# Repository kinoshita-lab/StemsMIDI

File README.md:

# STEMS MIDI: MIDI Controller for Traktor Stems (Dev board)

[日本語はこちら(Document in Japanese)](./README.ja.md)

## ChangeLog
### Software
releases (https://github.com/kinoshita-lab/StemsMIDI/releases)

### Hardware Rev. 1.1
- [Hardware] Remove center-click feature for Vol and Effect knobs
- [Hardware] Add testing terminals on PCB

## Kit Contents

- Pre-assembled PCB
- MCU Module Seeeduino XIAO RP2040(with flashed "sample" program)
- Pin Socket 1x7 (2 pcs.)
- Pin Header 1x7 (2 pcs.)
- Knob Caps (24 pcs.)
- Tactile switch Caps (24 pcs.)
- M3 Nuts (6 pcs.)
- M3 10mm Hex Spacers (6 pcs.)
- M3 7mm Hex Spacers (6 pcs.)
- M3 Screws (6 pcs.)
- Rubber feet pads(4 pcs.)
- Bottom Acrylic Panel (1 pcs.)
- Top Acrylic Panel (1 pcs.)

## Requied Equipments

- Solder Iron, Solder
- No.2 + Driver
- Plier and/or Wrench (for tightening nuts)

## How to assemble

### Assemble the MCU Module

Recommend following procedure to align pins.
tips: You can solder MCU Module directly on the PCBA board.

Solder Pin Sockets, Pin Headers, and MCU. 1st, combine Pin Sockets and Headers as show below:

Put above result into MCU's both side holes as shown below:

Put them on the holes of PCBA below:

Solder the Pin Header's MCU side:

Looks like below:

Put it again on the PCBA's holes:

Flip the PCBA board while holding the MCU module, with placing knob cap between MCU and the desk so that it can be held in place by its own weight.

Looks like below:

Solder all the Pin socket's pin:

### Assembling case

Peel off the protective sheet from the bottom acrylic panel, and attach nuts, M3  7mm Hex spacers hex screws (the shorter ones) at six locations.
(There are no two sides to the acrylic.):

Put PCBA bord on it, tighten with the M3 10mm hex screws (the longer ones).
Tighten each screw little by little at to align the overall position:

Peel of the protective sheet from top acrylic panel and put it on the PCBA.
Tighten them with M3 screws.
Again, tighten each screw little by little at to align the overall position:

Put rubber feets on the bottom:

Place knob caps:

Place tactile switch caps:

## Usage

- Connect the product to PC/MAC.
- Import .tsi file below on Traktor.

<https://github.com/kinoshita-lab/StemsMIDI/tree/main/Traktor%20Setting>

## How to update Software

What you will need:

- Latest software to be flashed to the MCU(firmware.uf2) download from <https://github.com/kinoshita-lab/StemsMIDI/releases>
- PC or mac

Connect the USB cable with pressing the **B** button on the right bottom of the MCU.

After releasing the button, disk drive will appear on you PC/mac. The drive name is `RP-RP2`.

Copy the firmware.uf2 file to the drive.

Done updating, drive will automatically closed.

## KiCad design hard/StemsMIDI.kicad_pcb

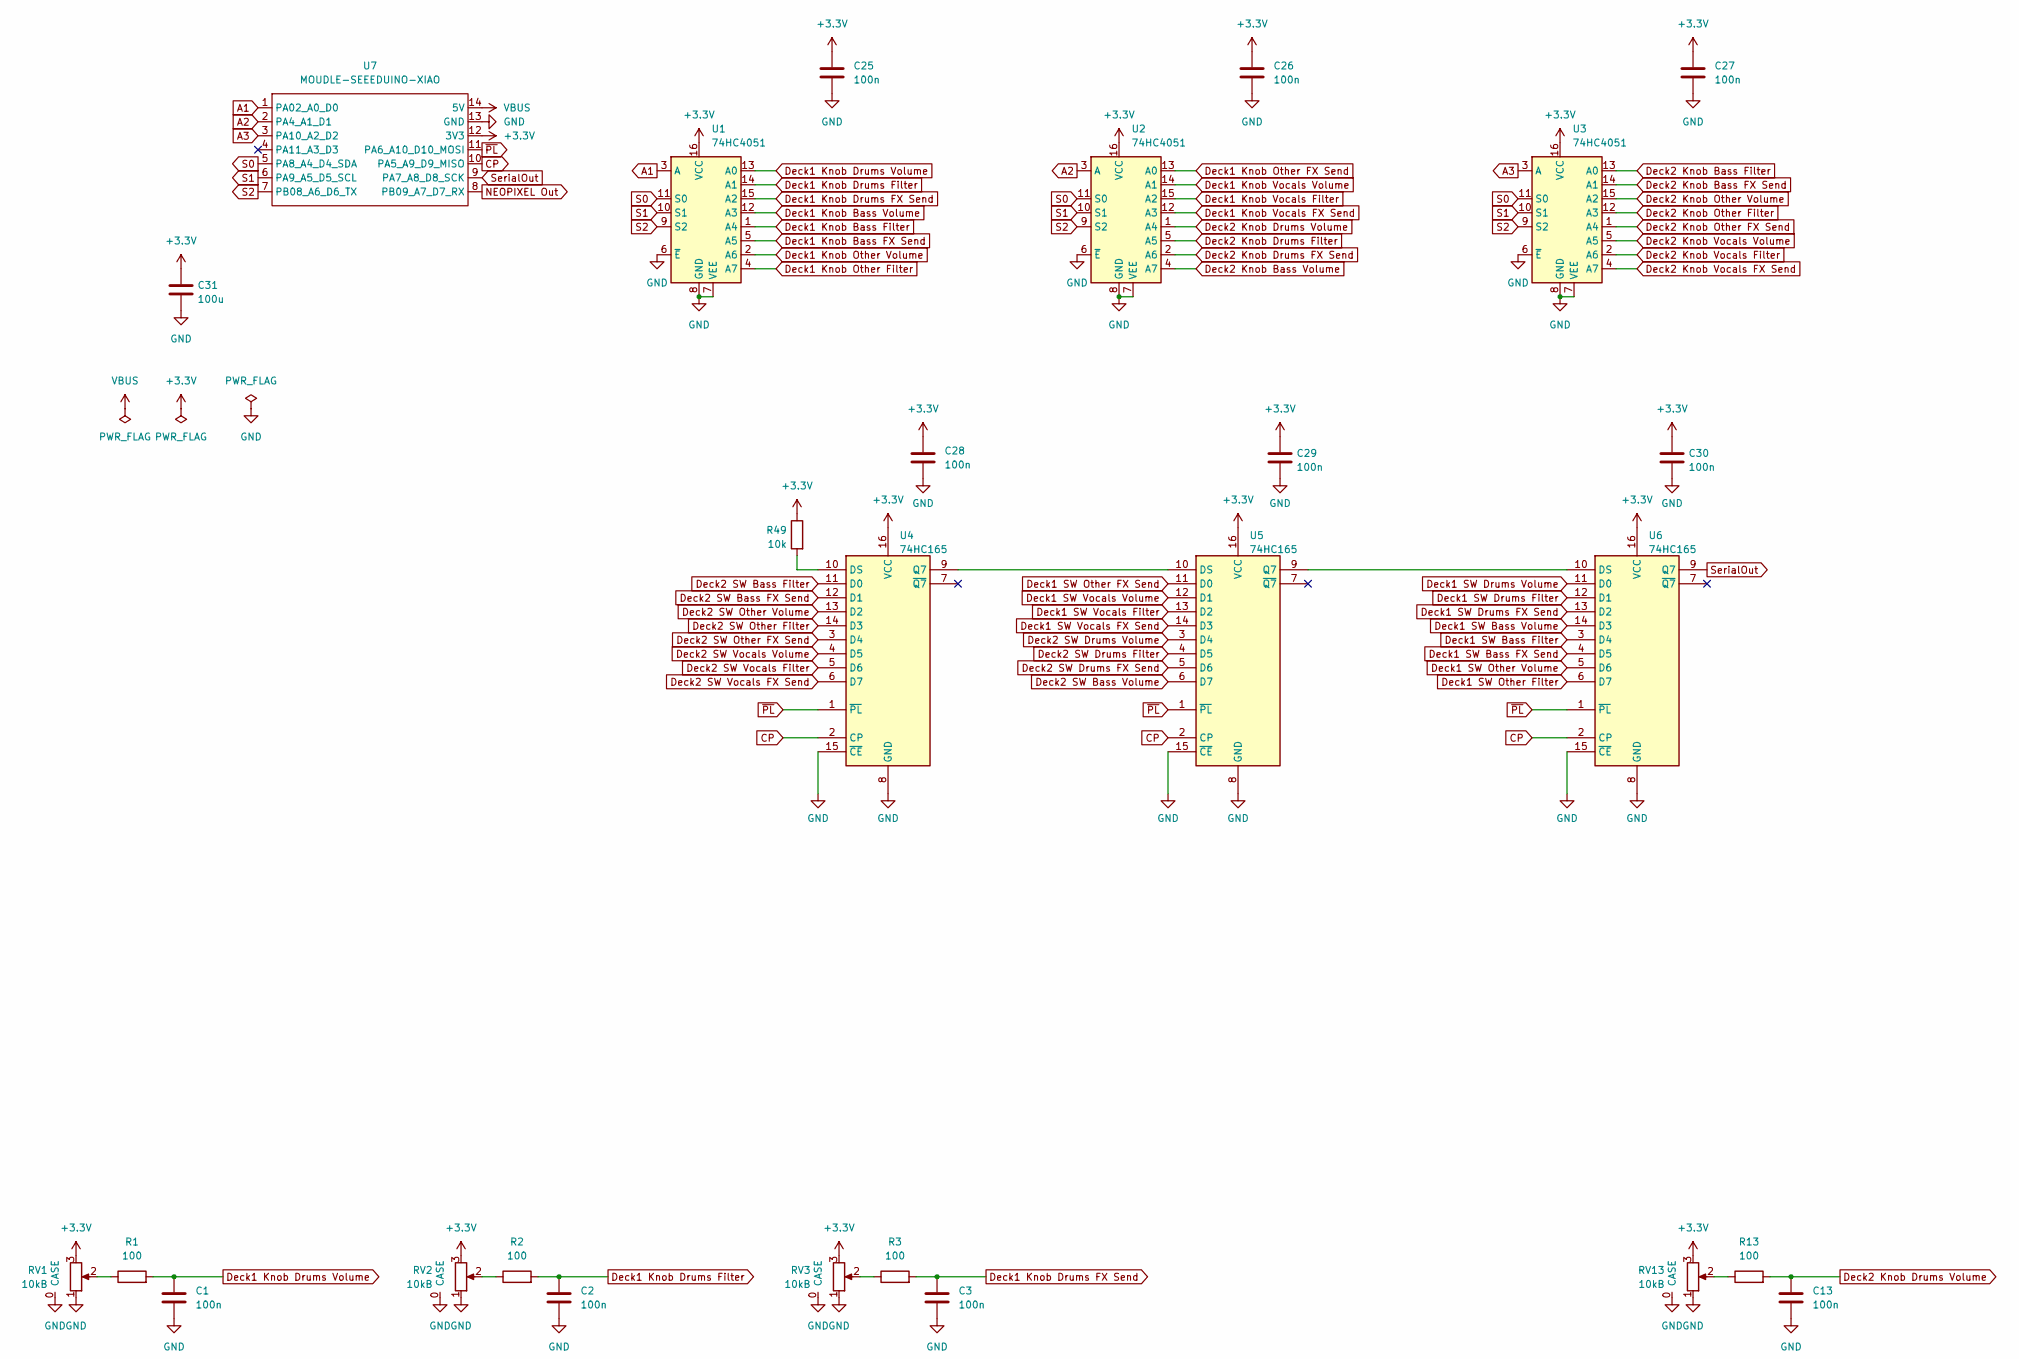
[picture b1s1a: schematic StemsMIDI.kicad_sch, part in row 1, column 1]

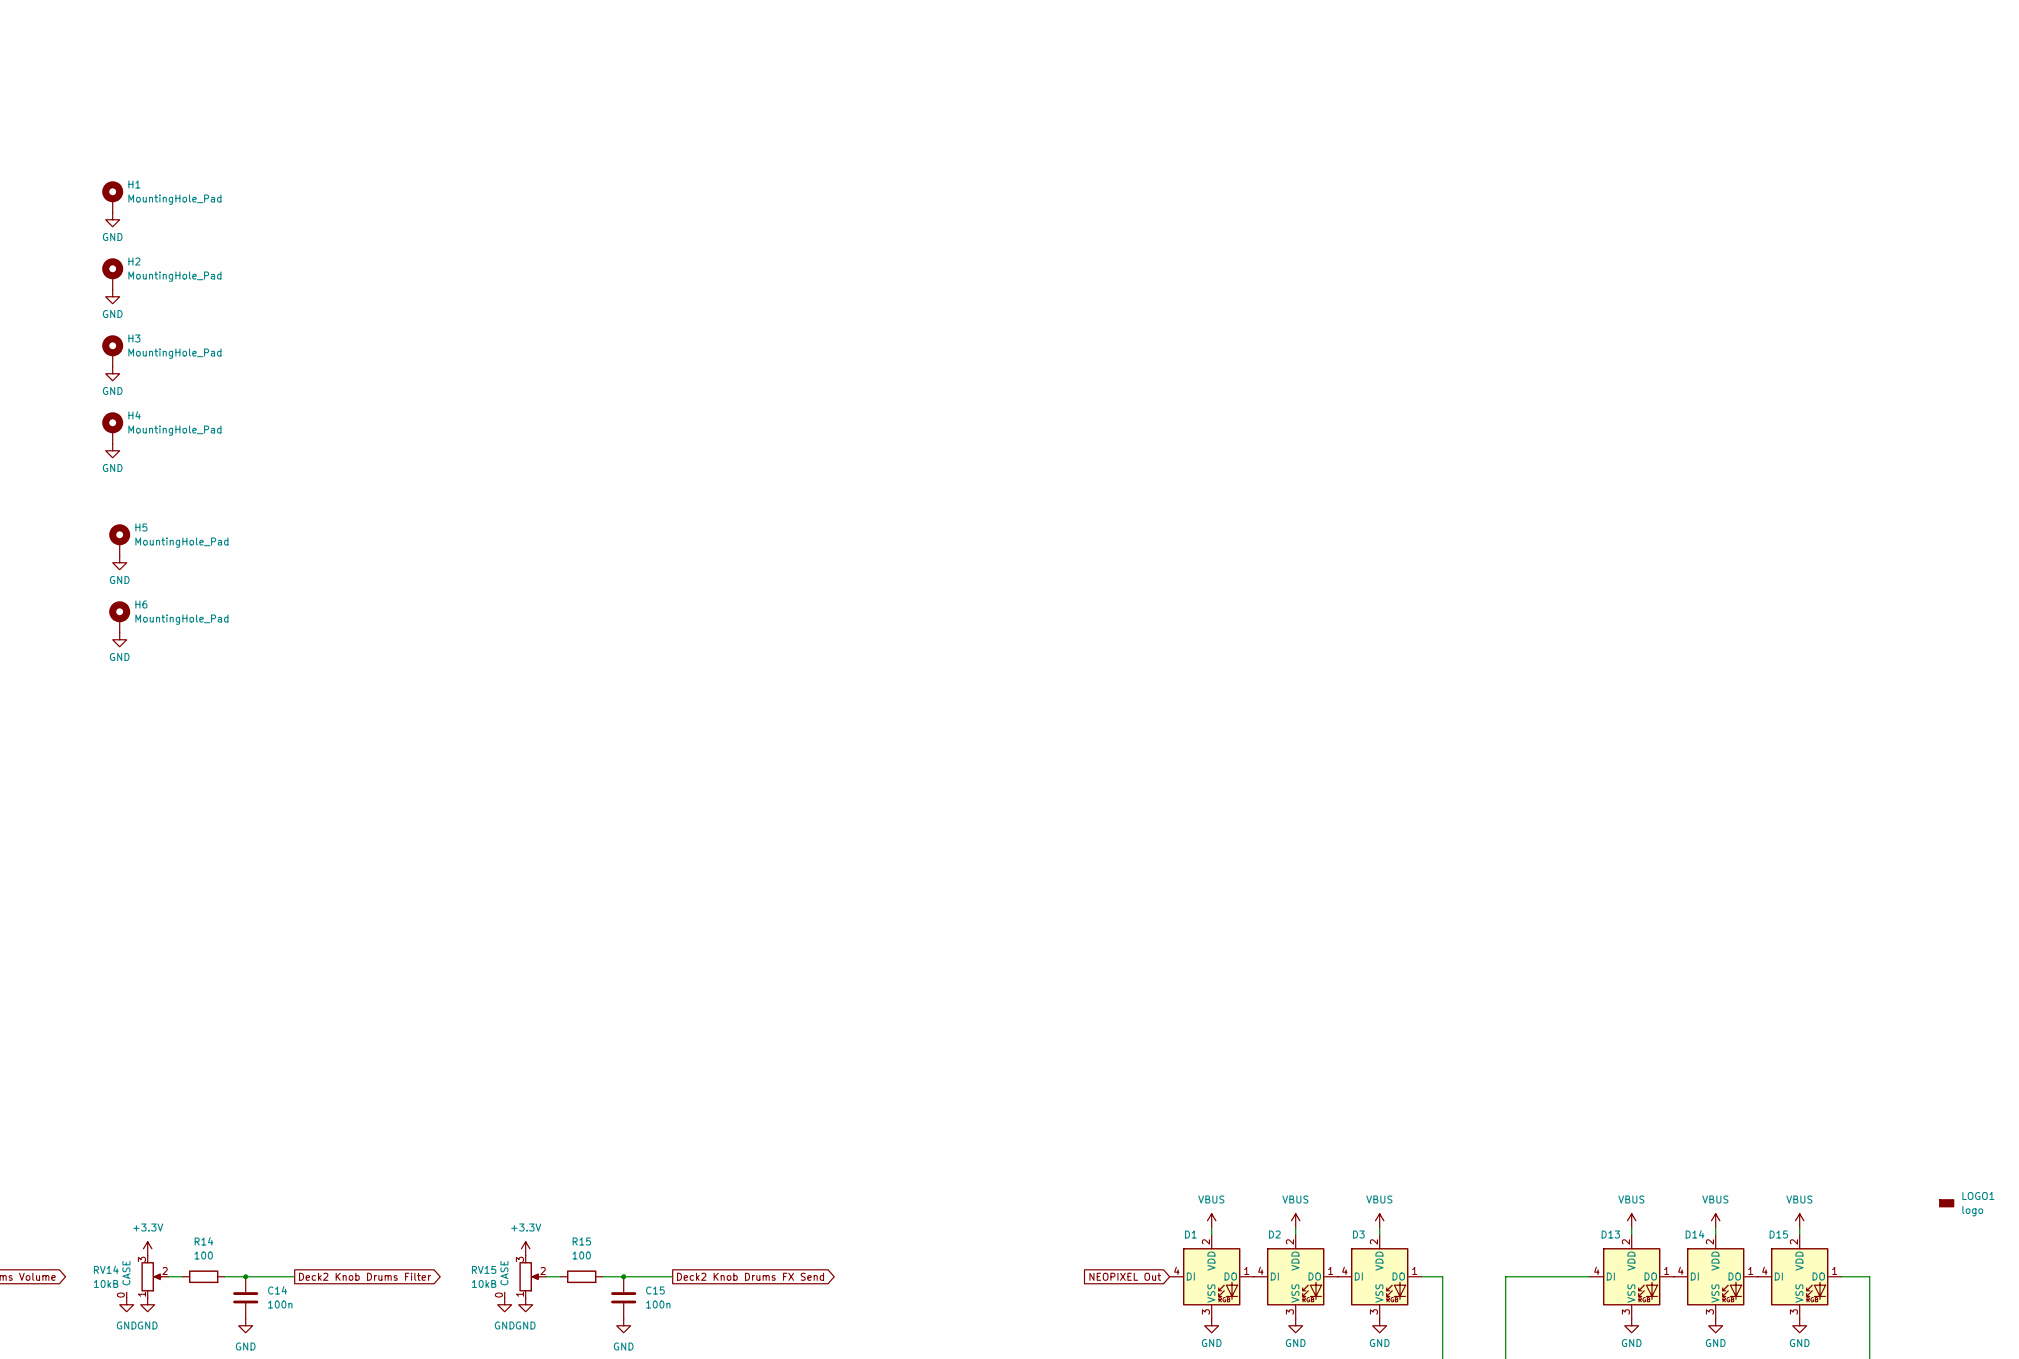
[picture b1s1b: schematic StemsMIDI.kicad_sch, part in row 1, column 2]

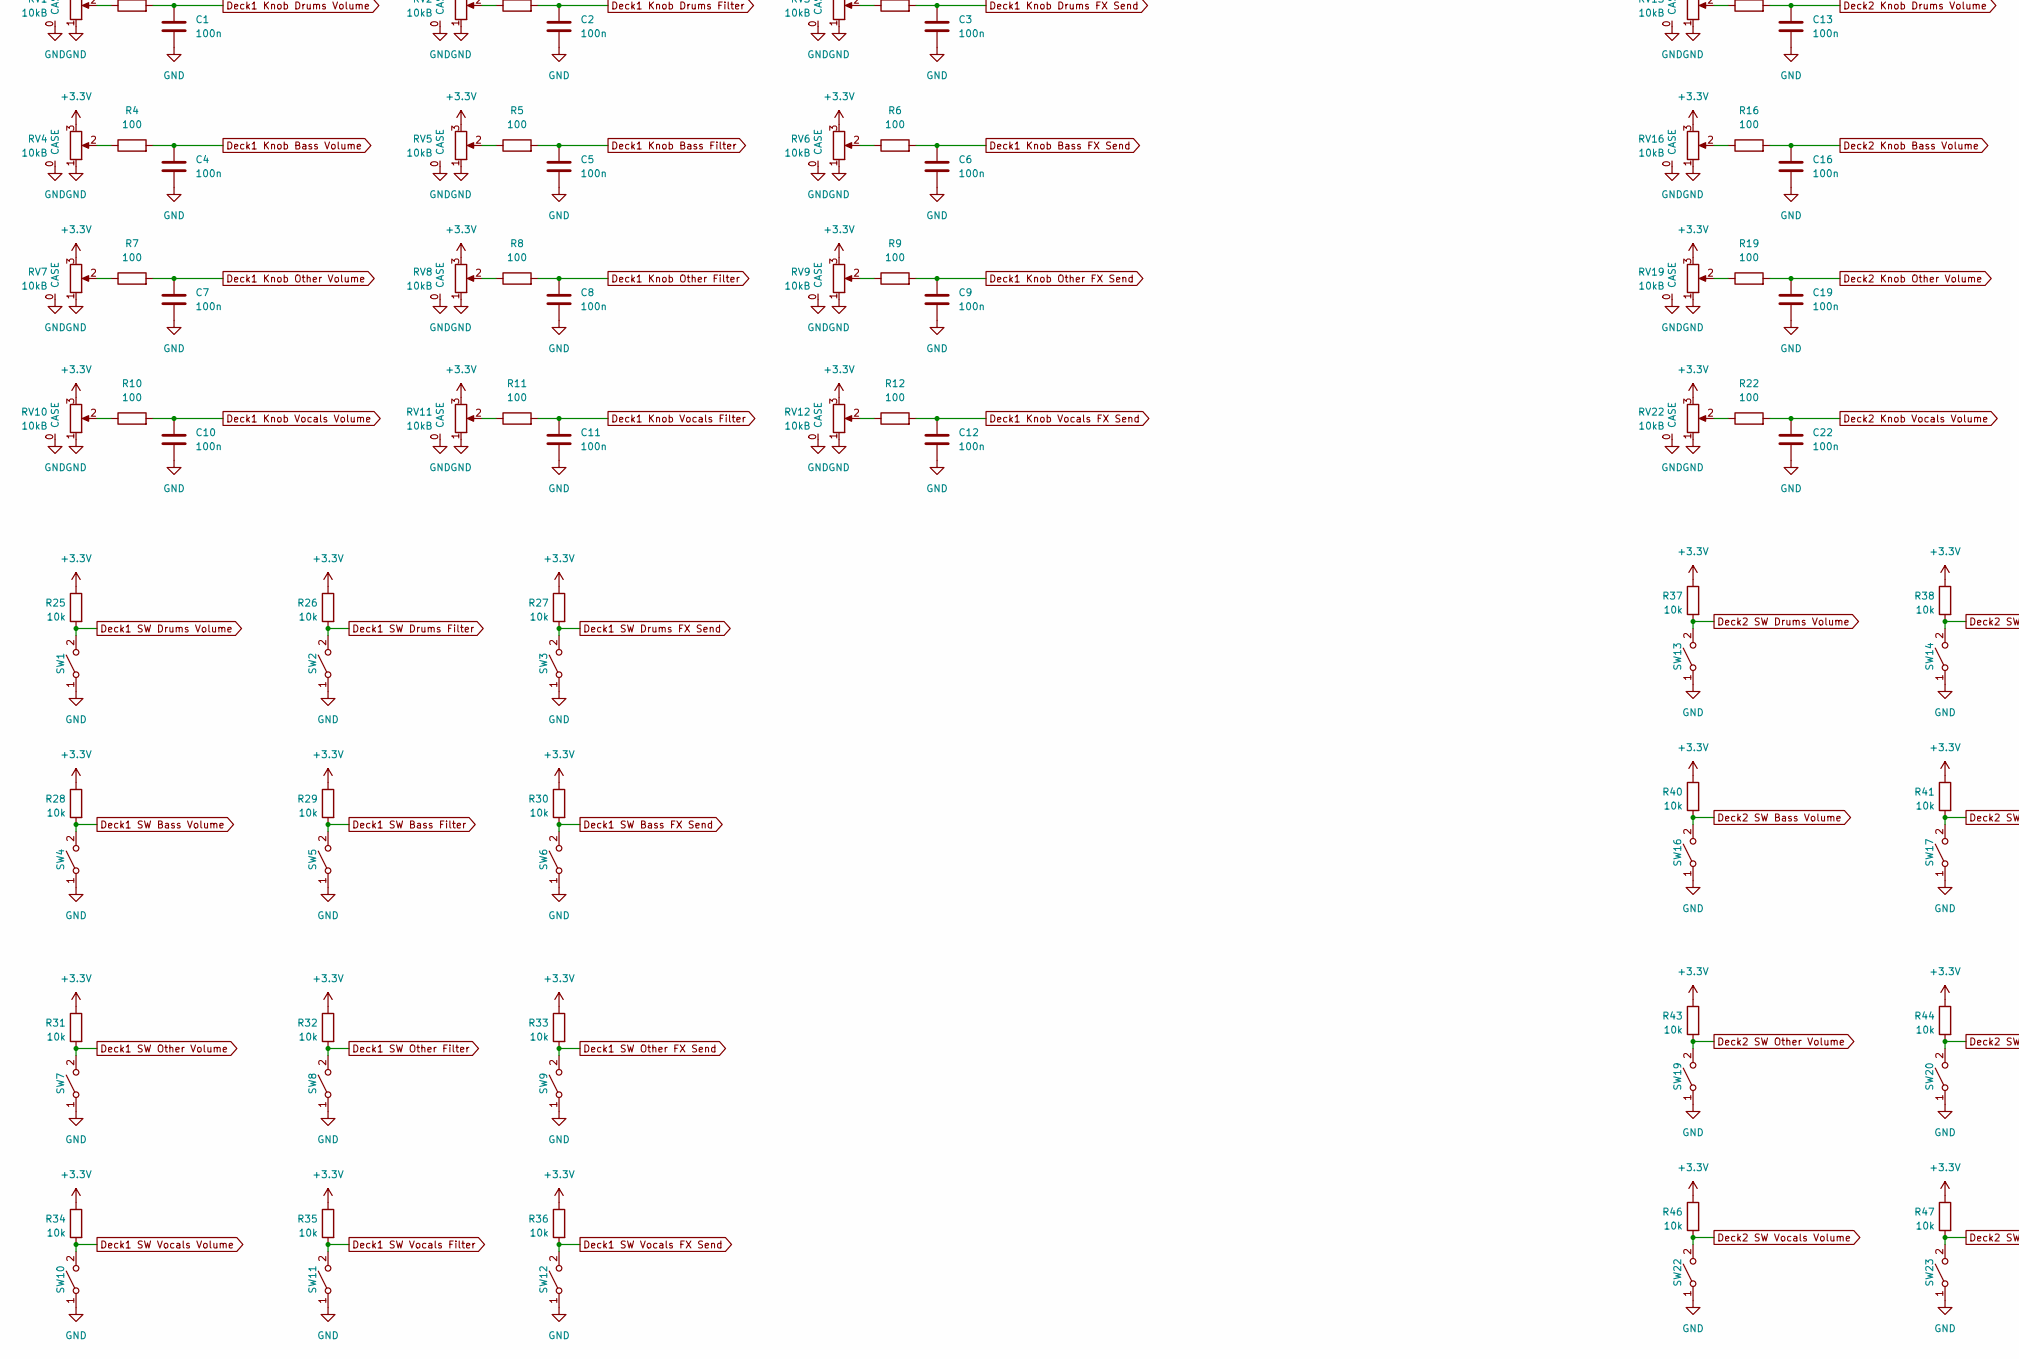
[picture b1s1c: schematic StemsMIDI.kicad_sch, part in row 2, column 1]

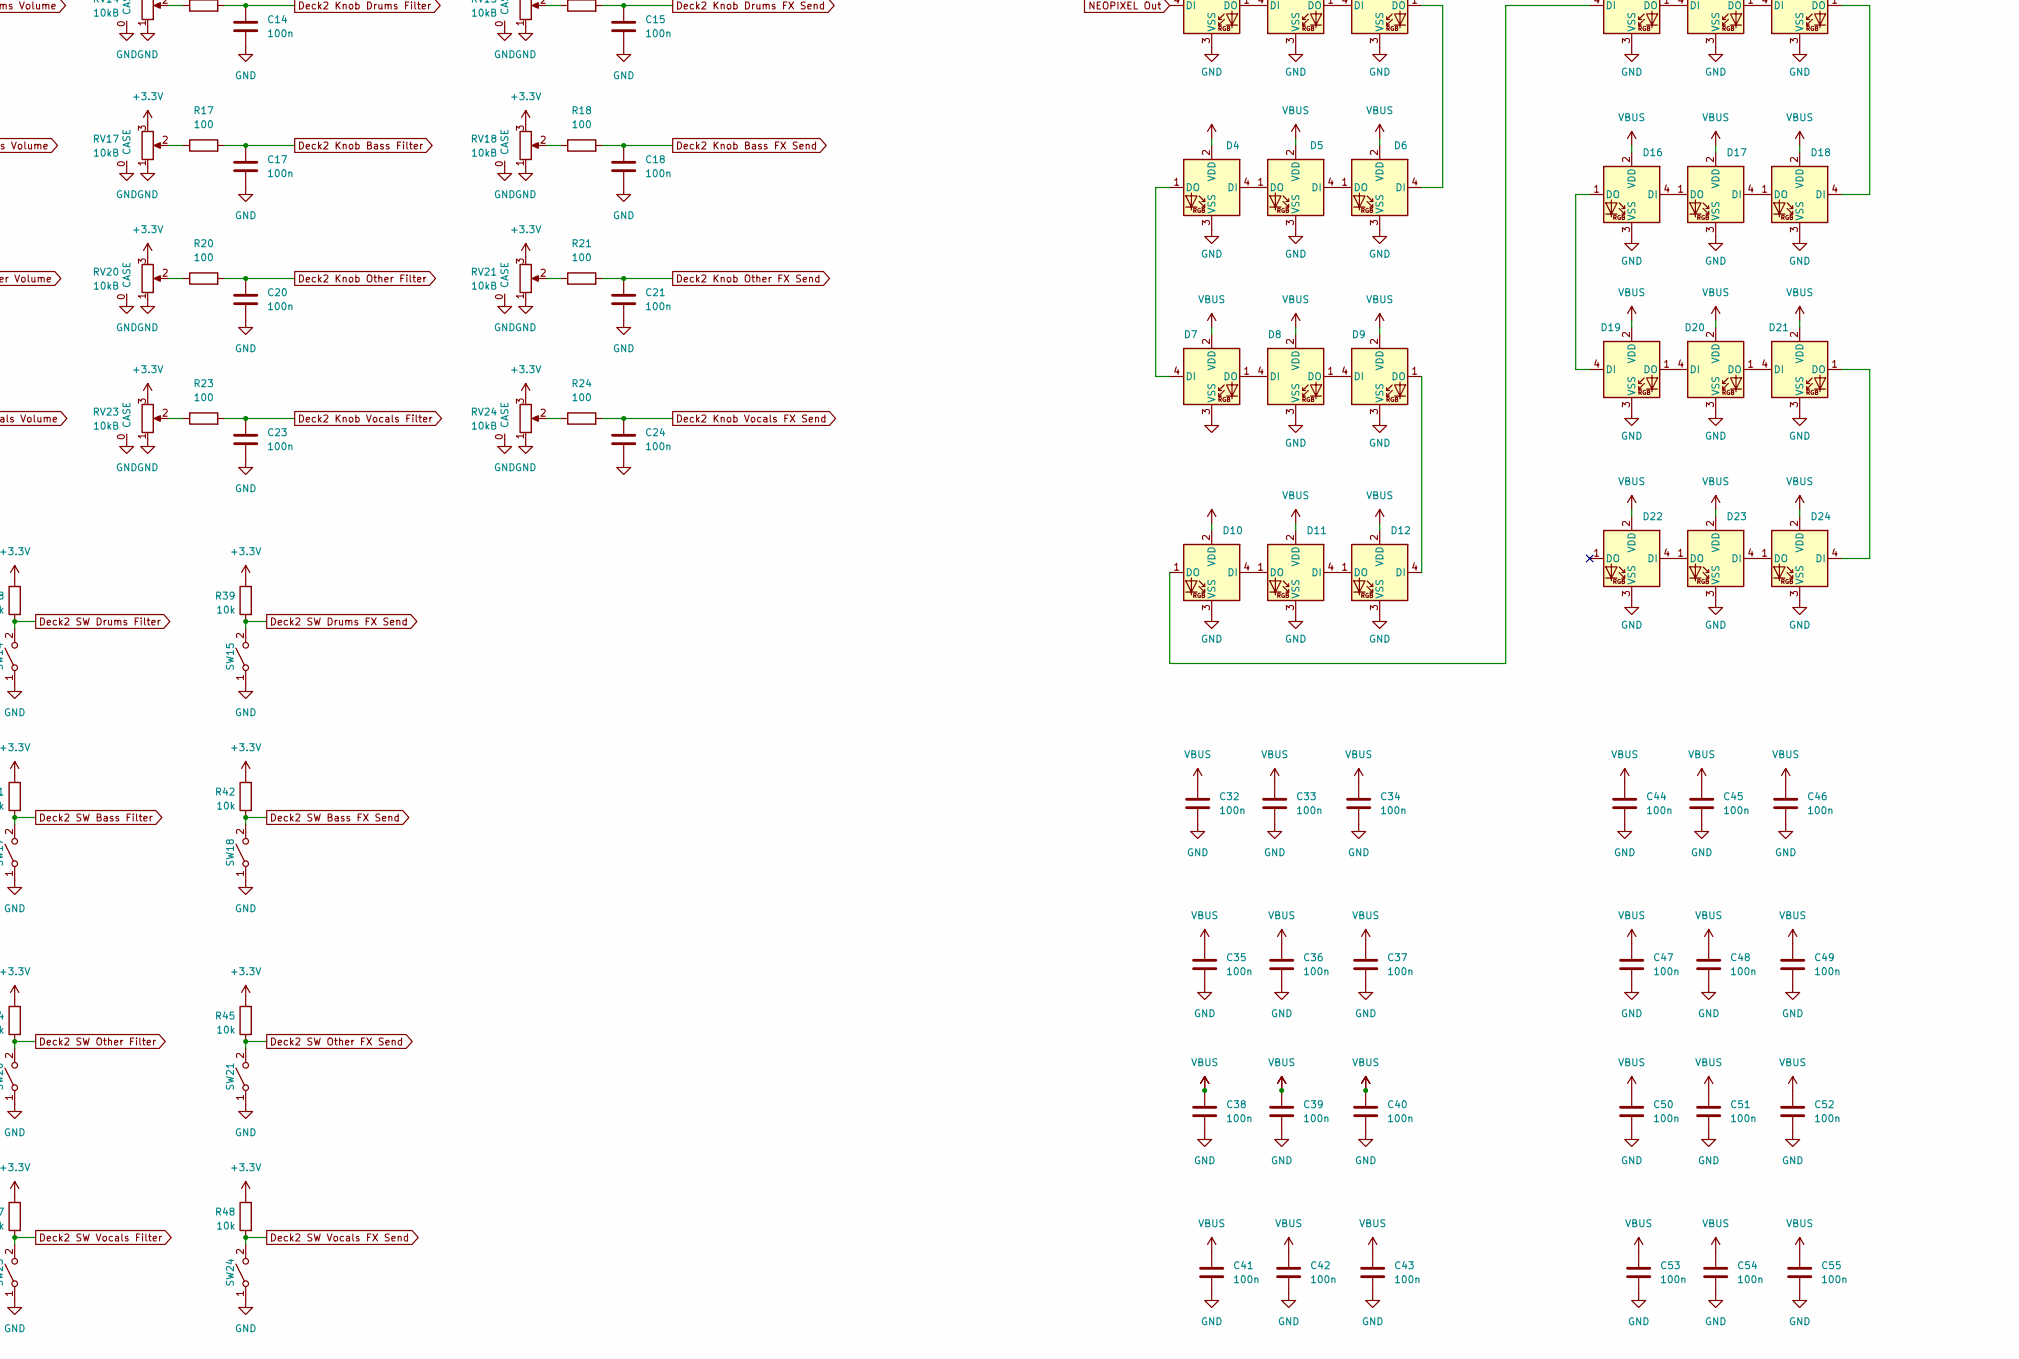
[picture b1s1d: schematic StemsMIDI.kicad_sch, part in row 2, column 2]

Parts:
C1, C2, C3, C4, C5, C6, C7, C8, C9, C10, C11, C12, C13, C14, C15, C16, C17, C18, C19, C20, C21, C22, C23, C24, C25, C26, C27, C28, C29, C30, C32, C33, C34, C35, C36, C37, C38, C39, C40, C41, C42, C43, C44, C45, C46, C47, C48, C49, C50, C51, C52, C53, C54, C55: 100n; C_0402_1005Metric_Pad0.74x0.62mm_HandSolder; LCSC C1525
C31: 100u; C_1206_3216Metric_Pad1.33x1.80mm_HandSolder; LCSC C312983
D1, D2, D3, D4, D5, D6, D7, D8, D9, D10, D11, D12, D13, D14, D15, D16, D17, D18, D19, D20, D21, D22, D23, D24: LED_NeoPixel_XL-1615RGBC-WS2812B; LCSC C5349954
H1, H2, H3, H4, H5, H6: MountingHole_Pad; MountingHole_3.2mm_M3_Pad
LOGO1: logo; kinoshita-logo_simplified_300dpi
R1, R2, R3, R4, R5, R6, R7, R8, R9, R10, R11, R12, R13, R14, R15, R16, R17, R18, R19, R20, R21, R22, R23, R24: 100; R_0402_1005Metric_Pad0.72x0.64mm_HandSolder; LCSC C106232
R25, R26, R27, R28, R29, R30, R31, R32, R33, R34, R35, R36, R37, R38, R39, R40, R41, R42, R43, R44, R45, R46, R47, R48, R49: 10k; R_0402_1005Metric_Pad0.72x0.64mm_HandSolder; LCSC C25744
RV1, RV2, RV3, RV4, RV5, RV6, RV7, RV8, RV9, RV10, RV11, RV12, RV13, RV14, RV15, RV16, RV17, RV18, RV19, RV20, RV21, RV22, RV23, RV24: 10kB; Potentiometer_Alps_RK09K_Horizontal_CORRECTED; LCSC C470315
SW1, SW2, SW3, SW4, SW5, SW6, SW7, SW8, SW9, SW10, SW11, SW12, SW13, SW14, SW15, SW16, SW17, SW18, SW19, SW20, SW21, SW22, SW23, SW24: SW_SPST; SW_Tactile_6mm_x_6mm_Futsuuno_SMD; LCSC C2885193
U1, U2, U3: 74HC4051; TSSOP-16_4.4x5mm_P0.65mm; LCSC C5645
U4, U5, U6: 74HC165; TSSOP-16_4.4x5mm_P0.65mm; LCSC C80696
U7: MOUDLE-SEEEDUINO-XIAO; Seeduino_Xiao_RP2040_MOUDLE14P-2.54-21X17.8MM

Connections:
+3.3V: C25.1, C26.1, C27.1, C28.1, C29.1, C30.1, C31.1, R25.1, R26.1, R27.1, R28.1, R29.1, R30.1, R31.1, R32.1, R33.1, R34.1, R35.1, R36.1, R37.1, R38.1, R39.1, R40.1, R41.1, R42.1, R43.1, R44.1, R45.1, R46.1, R47.1, R48.1, R49.1, RV1.3, RV2.3, RV3.3, RV4.3, RV5.3, RV6.3, RV7.3, RV8.3, RV9.3, RV10.3, RV11.3, RV12.3, RV13.3, RV14.3, RV15.3, RV16.3, RV17.3, RV18.3, RV19.3, RV20.3, RV21.3, RV22.3, RV23.3, RV24.3, U1.16 (VCC), U2.16 (VCC), U3.16 (VCC), U4.16 (VCC), U5.16 (VCC), U6.16 (VCC), U7.12 (3V3)
A1: U1.3 (A), U7.1 (PA02_A0_D0)
A2: U2.3 (A), U7.2 (PA4_A1_D1)
A3: U3.3 (A), U7.3 (PA10_A2_D2)
CP: U4.2 (CP), U5.2 (CP), U6.2 (CP), U7.10 (PA5_A9_D9_MISO)
Deck1 Knob Bass FX Send: C6.1, R6.2, U1.5 (A5)
Deck1 Knob Bass Filter: C5.1, R5.2, U1.1 (A4)
Deck1 Knob Bass Volume: C4.1, R4.2, U1.12 (A3)
Deck1 Knob Drums FX Send: C3.1, R3.2, U1.15 (A2)
Deck1 Knob Drums Filter: C2.1, R2.2, U1.14 (A1)
Deck1 Knob Drums Volume: C1.1, R1.2, U1.13 (A0)
Deck1 Knob Other FX Send: C9.1, R9.2, U2.13 (A0)
Deck1 Knob Other Filter: C8.1, R8.2, U1.4 (A7)
Deck1 Knob Other Volume: C7.1, R7.2, U1.2 (A6)
Deck1 Knob Vocals FX Send: C12.1, R12.2, U2.12 (A3)
Deck1 Knob Vocals Filter: C11.1, R11.2, U2.15 (A2)
Deck1 Knob Vocals Volume: C10.1, R10.2, U2.14 (A1)
Deck1 SW Bass FX Send: R30.2, SW6.2 (B), U6.4 (D5)
Deck1 SW Bass Filter: R29.2, SW5.2 (B), U6.3 (D4)
Deck1 SW Bass Volume: R28.2, SW4.2 (B), U6.14 (D3)
Deck1 SW Drums FX Send: R27.2, SW3.2 (B), U6.13 (D2)
Deck1 SW Drums Filter: R26.2, SW2.2 (B), U6.12 (D1)
Deck1 SW Drums Volume: R25.2, SW1.2 (B), U6.11 (D0)
Deck1 SW Other FX Send: R33.2, SW9.2 (B), U5.11 (D0)
Deck1 SW Other Filter: R32.2, SW8.2 (B), U6.6 (D7)
Deck1 SW Other Volume: R31.2, SW7.2 (B), U6.5 (D6)
Deck1 SW Vocals FX Send: R36.2, SW12.2 (B), U5.14 (D3)
Deck1 SW Vocals Filter: R35.2, SW11.2 (B), U5.13 (D2)
Deck1 SW Vocals Volume: R34.2, SW10.2 (B), U5.12 (D1)
Deck2 Knob Bass FX Send: C18.1, R18.2, U3.14 (A1)
Deck2 Knob Bass Filter: C17.1, R17.2, U3.13 (A0)
Deck2 Knob Bass Volume: C16.1, R16.2, U2.4 (A7)
Deck2 Knob Drums FX Send: C15.1, R15.2, U2.2 (A6)
Deck2 Knob Drums Filter: C14.1, R14.2, U2.5 (A5)
Deck2 Knob Drums Volume: C13.1, R13.2, U2.1 (A4)
Deck2 Knob Other FX Send: C21.1, R21.2, U3.1 (A4)
Deck2 Knob Other Filter: C20.1, R20.2, U3.12 (A3)
Deck2 Knob Other Volume: C19.1, R19.2, U3.15 (A2)
Deck2 Knob Vocals FX Send: C24.1, R24.2, U3.4 (A7)
Deck2 Knob Vocals Filter: C23.1, R23.2, U3.2 (A6)
Deck2 Knob Vocals Volume: C22.1, R22.2, U3.5 (A5)
Deck2 SW Bass FX Send: R42.2, SW18.2 (B), U4.12 (D1)
Deck2 SW Bass Filter: R41.2, SW17.2 (B), U4.11 (D0)
Deck2 SW Bass Volume: R40.2, SW16.2 (B), U5.6 (D7)
Deck2 SW Drums FX Send: R39.2, SW15.2 (B), U5.5 (D6)
Deck2 SW Drums Filter: R38.2, SW14.2 (B), U5.4 (D5)
Deck2 SW Drums Volume: R37.2, SW13.2 (B), U5.3 (D4)
Deck2 SW Other FX Send: R45.2, SW21.2 (B), U4.3 (D4)
Deck2 SW Other Filter: R44.2, SW20.2 (B), U4.14 (D3)
Deck2 SW Other Volume: R43.2, SW19.2 (B), U4.13 (D2)
Deck2 SW Vocals FX Send: R48.2, SW24.2 (B), U4.6 (D7)
Deck2 SW Vocals Filter: R47.2, SW23.2 (B), U4.5 (D6)
Deck2 SW Vocals Volume: R46.2, SW22.2 (B), U4.4 (D5)
GND: C1.2, C2.2, C3.2, C4.2, C5.2, C6.2, C7.2, C8.2, C9.2, C10.2, C11.2, C12.2, C13.2, C14.2, C15.2, C16.2, C17.2, C18.2, C19.2, C20.2, C21.2, C22.2, C23.2, C24.2, C25.2, C26.2, C27.2, C28.2, C29.2, C30.2, C31.2, C32.2, C33.2, C34.2, C35.2, C36.2, C37.2, C38.2, C39.2, C40.2, C41.2, C42.2, C43.2, C44.2, C45.2, C46.2, C47.2, C48.2, C49.2, C50.2, C51.2, C52.2, C53.2, C54.2, C55.2, D1.3 (VSS), D2.3 (VSS), D3.3 (VSS), D4.3 (VSS), D5.3 (VSS), D6.3 (VSS), D7.3 (VSS), D8.3 (VSS), D9.3 (VSS), D10.3 (VSS), D11.3 (VSS), D12.3 (VSS), D13.3 (VSS), D14.3 (VSS), D15.3 (VSS), D16.3 (VSS), D17.3 (VSS), D18.3 (VSS), D19.3 (VSS), D20.3 (VSS), D21.3 (VSS), D22.3 (VSS), D23.3 (VSS), D24.3 (VSS), H1.1, H2.1, H3.1, H4.1, H5.1, H6.1, RV1.0 (CASE), RV1.1, RV2.0 (CASE), RV2.1, RV3.0 (CASE), RV3.1, RV4.0 (CASE), RV4.1, RV5.0 (CASE), RV5.1, RV6.0 (CASE), RV6.1, RV7.0 (CASE), RV7.1, RV8.0 (CASE), RV8.1, RV9.0 (CASE), RV9.1, RV10.0 (CASE), RV10.1, RV11.0 (CASE), RV11.1, RV12.0 (CASE), RV12.1, RV13.0 (CASE), RV13.1, RV14.0 (CASE), RV14.1, RV15.0 (CASE), RV15.1, RV16.0 (CASE), RV16.1, RV17.0 (CASE), RV17.1, RV18.0 (CASE), RV18.1, RV19.0 (CASE), RV19.1, RV20.0 (CASE), RV20.1, RV21.0 (CASE), RV21.1, RV22.0 (CASE), RV22.1, RV23.0 (CASE), RV23.1, RV24.0 (CASE), RV24.1, SW1.1 (A), SW2.1 (A), SW3.1 (A), SW4.1 (A), SW5.1 (A), SW6.1 (A), SW7.1 (A), SW8.1 (A), SW9.1 (A), SW10.1 (A), SW11.1 (A), SW12.1 (A), SW13.1 (A), SW14.1 (A), SW15.1 (A), SW16.1 (A), SW17.1 (A), SW18.1 (A), SW19.1 (A), SW20.1 (A), SW21.1 (A), SW22.1 (A), SW23.1 (A), SW24.1 (A), U1.6 (~E), U1.7 (VEE), U1.8 (GND), U2.6 (~E), U2.7 (VEE), U2.8 (GND), U3.6 (~E), U3.7 (VEE), U3.8 (GND), U4.8 (GND), U4.15 (~CE), U5.8 (GND), U5.15 (~CE), U6.8 (GND), U6.15 (~CE), U7.13 (GND)
NEOPIXEL Out: D1.4 (DI), U7.8 (PB09_A7_D7_RX)
unnamed: D1.1 (DO), D2.4 (DI)
unnamed: D2.1 (DO), D3.4 (DI)
unnamed: D3.1 (DO), D6.4 (DI)
unnamed: D4.4 (DI), D5.1 (DO)
unnamed: D4.1 (DO), D7.4 (DI)
unnamed: D5.4 (DI), D6.1 (DO)
unnamed: D7.1 (DO), D8.4 (DI)
unnamed: D8.1 (DO), D9.4 (DI)
unnamed: D10.4 (DI), D11.1 (DO)
unnamed: D10.1 (DO), D13.4 (DI)
unnamed: D11.4 (DI), D12.1 (DO)
unnamed: D9.1 (DO), D12.4 (DI)
unnamed: D13.1 (DO), D14.4 (DI)
unnamed: D14.1 (DO), D15.4 (DI)
unnamed: D15.1 (DO), D18.4 (DI)
unnamed: D16.4 (DI), D17.1 (DO)
unnamed: D16.1 (DO), D19.4 (DI)
unnamed: D17.4 (DI), D18.1 (DO)
unnamed: D19.1 (DO), D20.4 (DI)
unnamed: D20.1 (DO), D21.4 (DI)
unnamed: D21.1 (DO), D24.4 (DI)
unnamed: D22.4 (DI), D23.1 (DO)
unnamed: D23.4 (DI), D24.1 (DO)
unnamed: R1.1, RV1.2
unnamed: R2.1, RV2.2
unnamed: R3.1, RV3.2
unnamed: R4.1, RV4.2
unnamed: R5.1, RV5.2
unnamed: R6.1, RV6.2
unnamed: R7.1, RV7.2
unnamed: R8.1, RV8.2
unnamed: R9.1, RV9.2
unnamed: R10.1, RV10.2
unnamed: R11.1, RV11.2
unnamed: R12.1, RV12.2
unnamed: R13.1, RV13.2
unnamed: R14.1, RV14.2
unnamed: R15.1, RV15.2
unnamed: R16.1, RV16.2
unnamed: R17.1, RV17.2
unnamed: R18.1, RV18.2
unnamed: R19.1, RV19.2
unnamed: R20.1, RV20.2
unnamed: R21.1, RV21.2
unnamed: R22.1, RV22.2
unnamed: R23.1, RV23.2
unnamed: R24.1, RV24.2
unnamed: R49.2, U4.10 (DS)
unnamed: U4.9 (Q7), U5.10 (DS)
unnamed: U5.9 (Q7), U6.10 (DS)
S0: U1.11 (S0), U2.11 (S0), U3.11 (S0), U7.5 (PA8_A4_D4_SDA)
S1: U1.10 (S1), U2.10 (S1), U3.10 (S1), U7.6 (PA9_A5_D5_SCL)
S2: U1.9 (S2), U2.9 (S2), U3.9 (S2), U7.7 (PB08_A6_D6_TX)
SerialOut: U6.9 (Q7), U7.9 (PA7_A8_D8_SCK)
VBUS: C32.1, C33.1, C34.1, C35.1, C36.1, C37.1, C38.1, C39.1, C40.1, C41.1, C42.1, C43.1, C44.1, C45.1, C46.1, C47.1, C48.1, C49.1, C50.1, C51.1, C52.1, C53.1, C54.1, C55.1, D1.2 (VDD), D2.2 (VDD), D3.2 (VDD), D4.2 (VDD), D5.2 (VDD), D6.2 (VDD), D7.2 (VDD), D8.2 (VDD), D9.2 (VDD), D10.2 (VDD), D11.2 (VDD), D12.2 (VDD), D13.2 (VDD), D14.2 (VDD), D15.2 (VDD), D16.2 (VDD), D17.2 (VDD), D18.2 (VDD), D19.2 (VDD), D20.2 (VDD), D21.2 (VDD), D22.2 (VDD), D23.2 (VDD), D24.2 (VDD), U7.14 (5V)
~PL: U4.1 (~PL), U5.1 (~PL), U6.1 (~PL), U7.11 (PA6_A10_D10_MOSI)

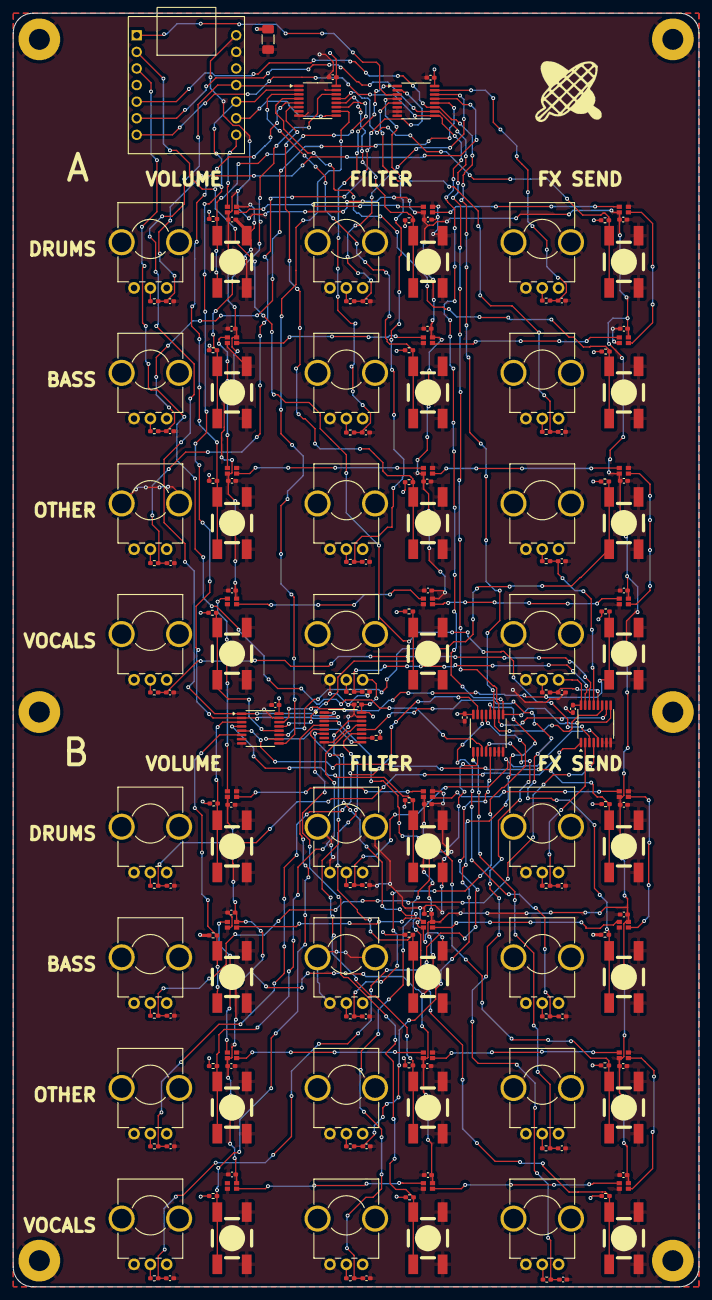
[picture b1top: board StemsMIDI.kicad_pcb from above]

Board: 2 copper layers, 105.0 x 195.0 mm, 190 parts (0 on the bottom side), 111 nets.

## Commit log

2024-11-02 add hardware files
2024-11-02 soft: under development. implement knob w/ table
2024-11-02 soft: implement swith scan
2024-11-06 add traktor settings
2024-11-06 implement LED
2024-11-06 Correct traktor settings
2024-11-10 add README, README.ja
2024-11-10 correct links
2024-11-10 add images
2024-11-10 README.ja.md の更新
2024-11-15 modify for rev 1.1
2024-11-19 Create LICENSE
2024-11-23 Update ja document
2024-12-02 [soft] add manufacture, product, serial
2024-12-02 [hard] Correct LCSC #
2024-12-02 Add How to assemble in Engligh
2024-12-28 revise readme for rev. 1.1
2024-12-29 implement product testing
2024-12-29 remove cards
2024-12-29 add .gitignore
2024-12-29 add how to update software
2024-12-31 revert Serial disabling, due to the suspect that Serial.end() disables all the USB device features.
2025-04-05 [soft] remove center click plateau for knobs other than filters
2025-04-05 [case] reorganize, rename case and pcb files
